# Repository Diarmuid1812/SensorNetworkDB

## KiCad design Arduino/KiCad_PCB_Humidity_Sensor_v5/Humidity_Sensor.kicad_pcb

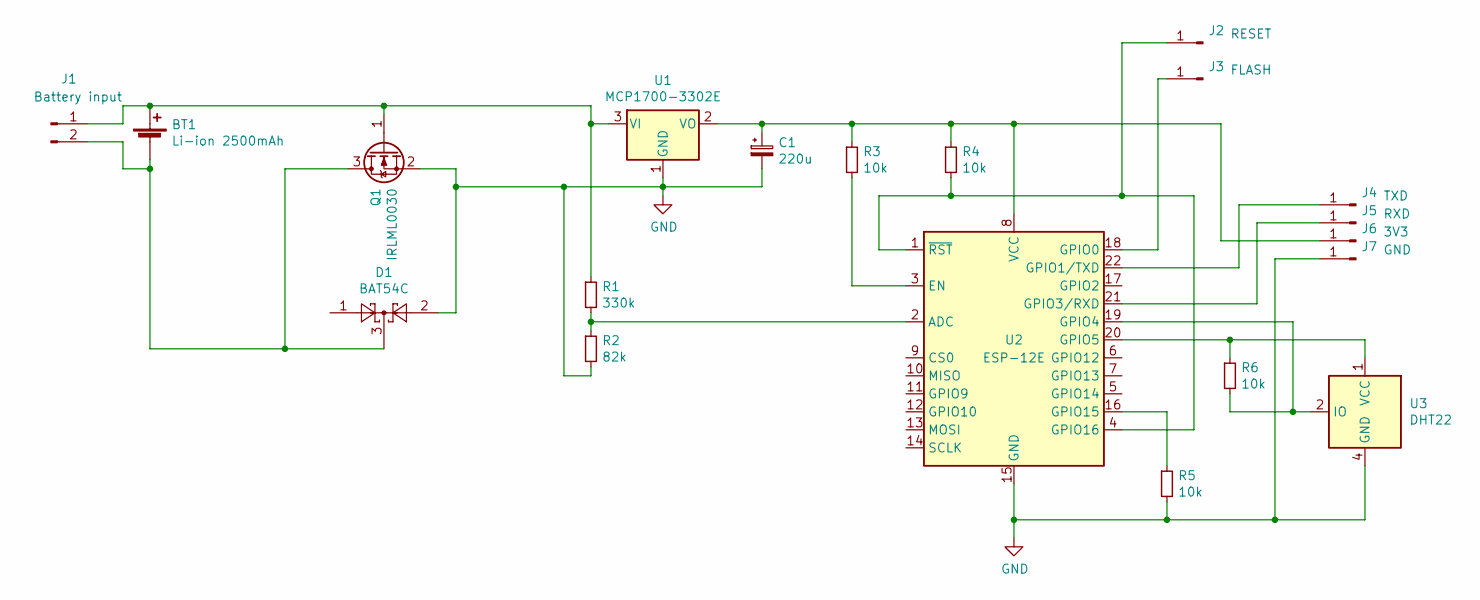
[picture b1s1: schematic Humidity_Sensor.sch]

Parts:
BT1: Li-ion 2500mAh; PinHeader_1x02_P2.54mm_Vertical
C1: 220u; CP_Elec_6.3x7.7
D1: BAT54C; SOT-23
J1: Battery input; PinHeader_1x02_P2.54mm_Vertical
J2: RESET; PinHeader_1x01_P2.54mm_Vertical
J3: FLASH; PinHeader_1x01_P2.54mm_Vertical
J4: TXD; PinHeader_1x01_P2.54mm_Vertical
J5: RXD; PinHeader_1x01_P2.54mm_Vertical
J6: 3V3; PinHeader_1x01_P2.54mm_Vertical
J7: GND; PinHeader_1x01_P2.54mm_Vertical
Q1: IRLML0030; SOT-23
R1: 330k; R_1206_3216Metric
R2: 82k; R_1206_3216Metric
R3, R4, R5, R6: 10k; R_1206_3216Metric
U1: MCP1700-3302E; SOT-23
U2: ESP-12E
U3: DHT22; Aosong_DHT11_5.5x12.0_P2.54mm

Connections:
GND: C1.2, D1.2, J7.1, Q1.2 (S), R2.2, R5.2, U1.1 (GND), U2.15 (GND), U3.4 (GND)
unnamed: BT1.1 (+), J1.1, Q1.1 (G), R1.1, U1.3 (VI)
unnamed: BT1.2 (-), D1.3, J1.2, Q1.3 (D)
unnamed: C1.1, J6.1, R3.1, R4.1, U1.2 (VO), U2.8 (VCC)
unnamed: J2.1, R4.2, U2.1 (~RST), U2.4 (GPIO16)
unnamed: J3.1, U2.18 (GPIO0)
unnamed: J4.1, U2.22 (GPIO1/TXD)
unnamed: J5.1, U2.21 (GPIO3/RXD)
unnamed: R1.2, R2.1, U2.2 (ADC)
unnamed: R3.2, U2.3 (EN)
unnamed: R5.1, U2.16 (GPIO15)
unnamed: R6.1, U2.20 (GPIO5), U3.1 (VCC)
unnamed: R6.2, U2.19 (GPIO4), U3.2 (IO)

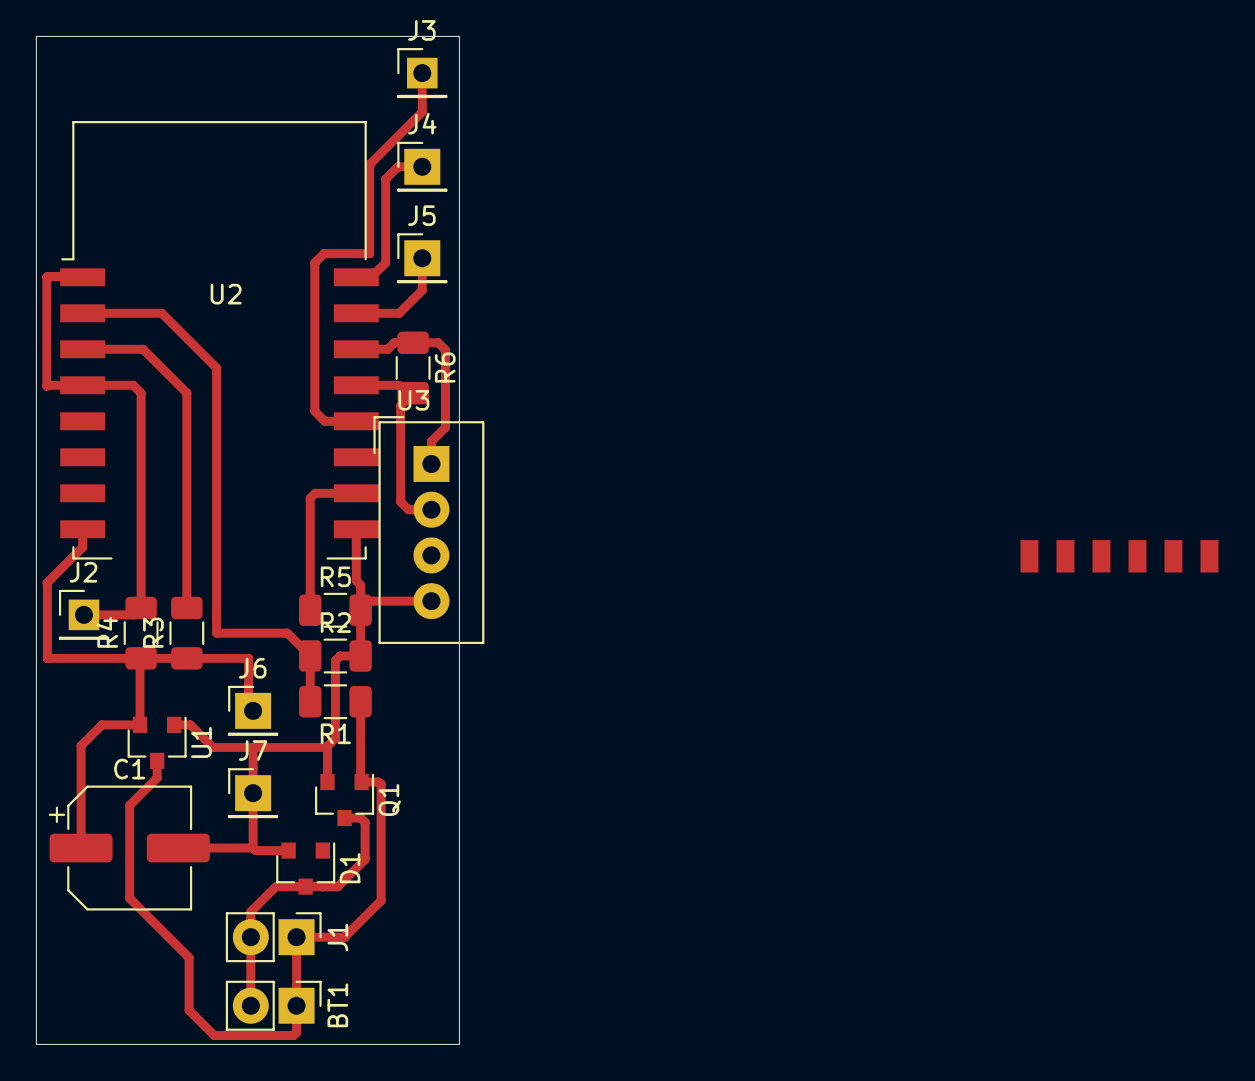
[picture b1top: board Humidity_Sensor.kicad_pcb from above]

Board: 2 copper layers, 23.5 x 56.0 mm, 20 parts (0 on the bottom side), 13 nets.

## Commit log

2020-04-03 Wszystko co miałem lokalnie
    Pierwsze przesłanie plików
2020-04-12 Dodano funkcje usuwania
    Dodano funkcje usuwania z uwzględnieniem trybu bezpiecznego.
    Do zrobienia: Sanityzacja, upewnienie się, że tryb bezpieczny jest domyślnie ustawiony, testy
2020-04-22 komunikacja i poprawienie dodania Todolist w komentarzach do komunikacji
2020-04-23 Wyświetlanie tabeli pomiarów
2020-04-23 Revert "Update workspace.xml"
    This reverts commit 9a216cbee8876dc5ae5f53271828b29051f00398.
2020-04-25 Zmiana na PDO i weryfikacja (1/2) Należy użyć PDO również przy wyświetlaniu tabel
2020-04-29 PDO (2/2) tabele
2020-04-29 Komunikacja do przetestowania
2020-05-02 Save before LoginTest
    Saving master befor test fork for login system
2020-05-02 Init Fork
2020-05-05 Prototyp 1 - nie gotowe Wymaga integracji, decyzji co do metody tworzenia hasła dla nowych użytkowników, wdrożenia do architektury aplikacji i użycia włsnego arkusza stylów.
2020-05-06 Wersja testowa
    Należy dodać poprawny mechanizm tworzenia pierwszego hasła (link / wysyłanie losowego na mail ?)
2020-05-07 Łączenie
2020-05-07 CSV prototyp
2020-05-10 Mail z pierwszym hasłem, data w com
2020-05-13 Działająca komunikacja
2020-05-15 Transakcej i zabezpieczenia dla bazy danych
2020-05-18 Tabela czujników -- integracja
2020-05-19 Program do czujnika
    + dodanie lokalnej ścieżki do biblioteki DHT22 i samej biblioteki
    + zapis i odczyt ssid i hasła z EEPROM, wymaga przetestowania
2020-05-19 Generacja Raportu
2020-05-22 Alarmy, poprawiona obsługa hasła Sprawdzenie czy komunikujący się czujnik jest w bazie Alarmy mailowe przy komunikacji Regex na znaki specjalne w haśle Sprawdzanie zmiany pierwszego hasła Potwierdzan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
2020-05-23 Dodanie konfiguracji adresu IP serwera
    Naprawiono błąd w odczycie danych z EEPROM
    Dodano możliwość konfiguracji adresu IP serwera przez port szeregowy
2020-05-24 Poprawione alarmy i czujnik.
2020-05-24 Admin i sprawdzanie zmiany hasła
2020-05-24 Nowe css
2020-05-24 Poprawiony raport
2020-05-24 Css do validate
2020-05-24 Juz wyglada jak interfejs
2020-05-24 Połączone linkami menu
2020-05-24 Interfejs czujniki
2020-05-25 Przyciski w raportach
2020-05-25 Wybudzanie czujnika co 6 godzin
    +wybudzanie czujnika co 6 godzin. Pamięć oparta jest na rejestrach RTC, dzięki czemu nie wypala EEPROM.
    +poprawienie błędu w zapisie adresu IP serwera w EEPROM
2020-05-26 poprawki po merge'u
2020-05-26 interfejsCzujniki dziala
2020-05-26 Naprawa po niespójnym merge'u
2020-05-26 Login i zabezpieczenia Logowanie do stron, potwierdzanie usunięcia czujnika za pomocą hasła, podział na opcje zwykłe i administratorskie
2020-05-27 Funkcja usuw. użytkowników, naprawy logowania
2020-05-27 Finalna wersja programu czujnika
    wersja programu dla ESP do wgrania na czujnik
2020-05-27 Informacje o błędach usuwania
2020-05-27 dodaj sie wreszcze
2020-05-27 poprawki estetyczne
2020-05-27 sortowanie wg. nr. czujnika
2020-05-27 usuniecie indeksow
2020-05-27 Integracja PHP, naprawa funkcji
2020-05-27 Kaskadowe usuwanie
2020-05-29 Zabezpieczenie rejestru czujnika przed błędną inicjalizacją
    Zabezpieczenie przed przypadkową inicjalizacją rejestru RTC wartością ujemną
2020-06-01 Backup, index
2020-06-01 Jednostki
2020-06-02 Zmiana relacji w BD
    Nr czujnika jest teraz referencją do numeru programowego
2020-06-02 Naprawa alarmów
2020-06-02 Naprawa po testach
2020-06-02 Restrukturyzacja, backupy bazy
2020-06-02 Wersja testowa
2020-06-02 Dodanie resetu czujnika do ustawień fabrycznych
    +dodanie opcji "x" resetującej ustawienia czujnika
    +poprawienie błędu w czekaniu na kolejne cykle uśpienia
    +zmiana wsółczynnika skalowania napięcia baterii
2020-06-06 Poprawka komunikatu o przywróceniu ustawień
    Komunikat o przywróceniu do ustawień fabrycznych wykonywał się w złym miejscu
2020-06-06 Po testach, komunikaty interfejsu czujników, bateria
    +Bateria w procentach, powyżej 5 %
    +Wyświetlanie jednostki
    +Poprawa nagłówka dla numeru czujnika
    +Komunikaty przy błędach dodania czujnika
    +Poprawione URL do komunikacji
2020-06-06 Naprawa złego wpisu do etykiet
2020-06-08 poprawa formatowania komunikatów
2020-06-08 Nowy układ, poprawa generacji raportu
    Tabele na stronie głównej obok siebie
    Naprawa błędu generacji raportu z obecnego dnia
    Zamykanie połączenia po dodaniu czujnika
2020-07-15 Timeout połączenia z wifi w czujniku
    + Dodano timeout przy próbie połączenia z wifi przez czujnik
    + Docelowy czas uśpienia ustawiono na 1 godzinę (komunikat co 6 godzin)
2020-07-20 Schemat i PCB czujnika
    Schemat i PCB czujnika w KiCad i wyeksportowane w PDF
2021-02-27 Poprawienie pomiaru stanu baterii
